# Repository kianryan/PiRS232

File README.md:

# PiRS232

PiRS232 is a Pi uHAT for interfacing with RS232 serial devices.  
It supports RTS/CTS, and null modem.

## Requirements

* [Kicad 6](https://www.kicad.org/)

## Datasheets

* [Sipex SP232EEP](https://assets.maxlinear.com/web/documents/sipex/datasheets/sp3222e_sp3232e.pdf) - Discontinued RS232/TTL converter in DIP.

## License

[MIT](https://choosealicense.com/licenses/mit/)

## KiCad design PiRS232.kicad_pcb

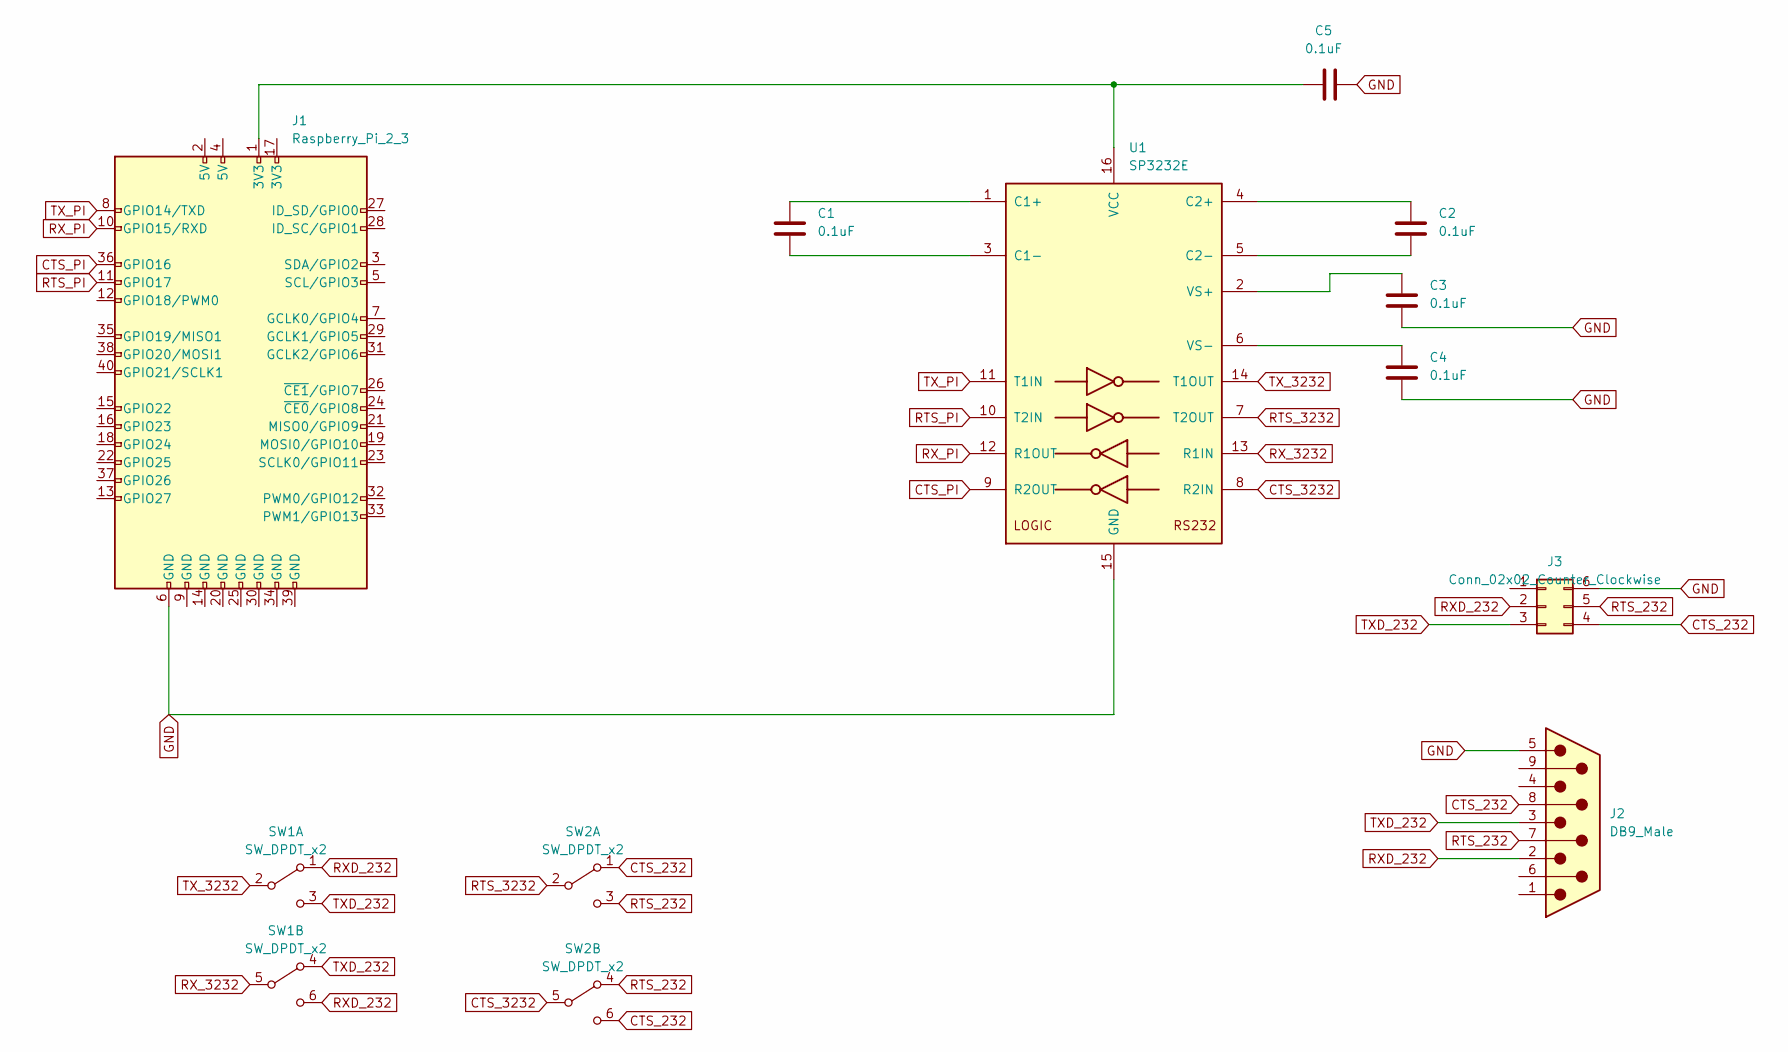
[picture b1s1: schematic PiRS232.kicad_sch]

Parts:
C1, C2, C3, C4, C5: 0.1uF; C_Disc_D5.0mm_W2.5mm_P5.00mm
J1: Raspberry_Pi_2_3; PinHeader_2x20_P2.54mm_Vertical
J2: DB9_Male; DSUB-9_Male_Horizontal_P2.77x2.84mm_EdgePinOffset4.94mm_Hou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
J3: Conn_02x02_Counter_Clockwise; PinHeader_2x03_P2.54mm_Vertical
SW1, SW2: SW_DPDT_x2; SW_CuK_JS202011AQN_DPDT_Angled
U1: SP3232E; DIP-16_W7.62mm

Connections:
CTS_232: J2.8, J3.4, SW2.1 (A), SW2.6 (C)
CTS_3232: SW2.5 (B), U1.8 (R2IN)
CTS_PI: J1.36 (GPIO16), U1.9 (R2OUT)
GND: C3.2, C4.2, C5.2, J1.6 (GND), J2.5, J3.6, U1.15 (GND)
unnamed: C1.1, U1.1 (C1+)
unnamed: C1.2, U1.3 (C1-)
unnamed: C2.1, U1.4 (C2+)
unnamed: C2.2, U1.5 (C2-)
unnamed: C3.1, U1.2 (VS+)
unnamed: C4.1, U1.6 (VS-)
unnamed: C5.1, J1.1 (3V3), U1.16 (VCC)
RTS_232: J2.7, J3.5, SW2.3 (C), SW2.4 (A)
RTS_3232: SW2.2 (B), U1.7 (T2OUT)
RTS_PI: J1.11 (GPIO17), U1.10 (T2IN)
RXD_232: J2.2, J3.2, SW1.1 (A), SW1.6 (C)
RX_3232: SW1.5 (B), U1.13 (R1IN)
RX_PI: J1.10 (GPIO15/RXD), U1.12 (R1OUT)
TXD_232: J2.3, J3.3, SW1.3 (C), SW1.4 (A)
TX_3232: SW1.2 (B), U1.14 (T1OUT)
TX_PI: J1.8 (GPIO14/TXD), U1.11 (T1IN)

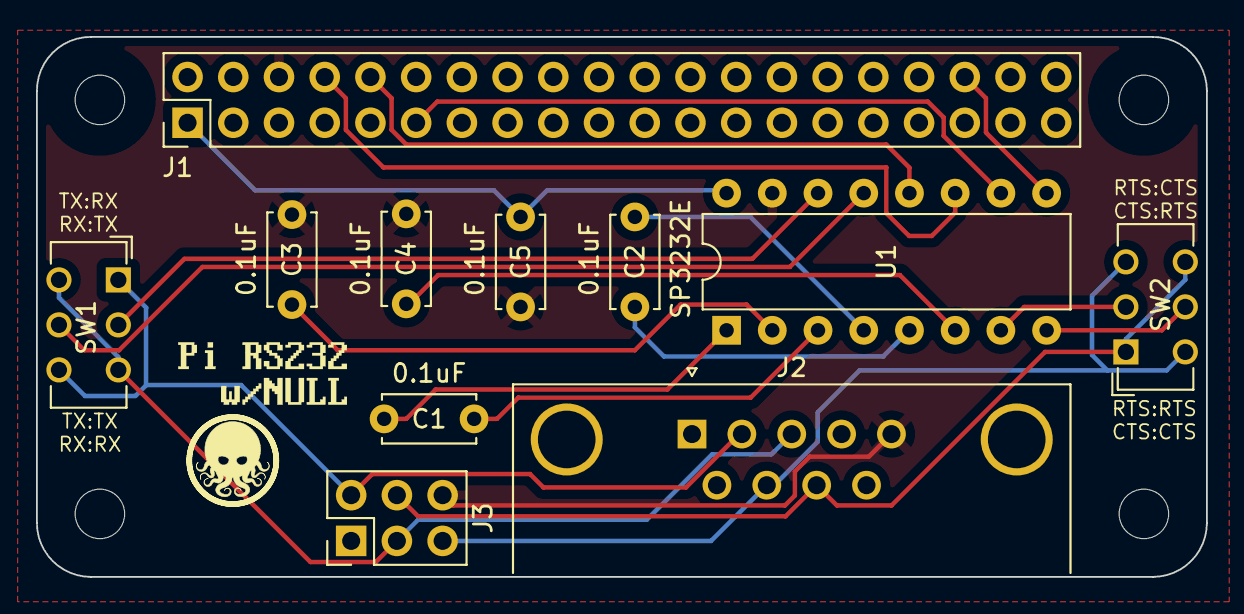
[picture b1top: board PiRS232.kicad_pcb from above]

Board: 2 copper layers, 65.0 x 30.0 mm, 11 parts (0 on the bottom side), 20 nets.

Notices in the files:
PiRS232.kicad_pcb:
©2022 Orange Tentacle
